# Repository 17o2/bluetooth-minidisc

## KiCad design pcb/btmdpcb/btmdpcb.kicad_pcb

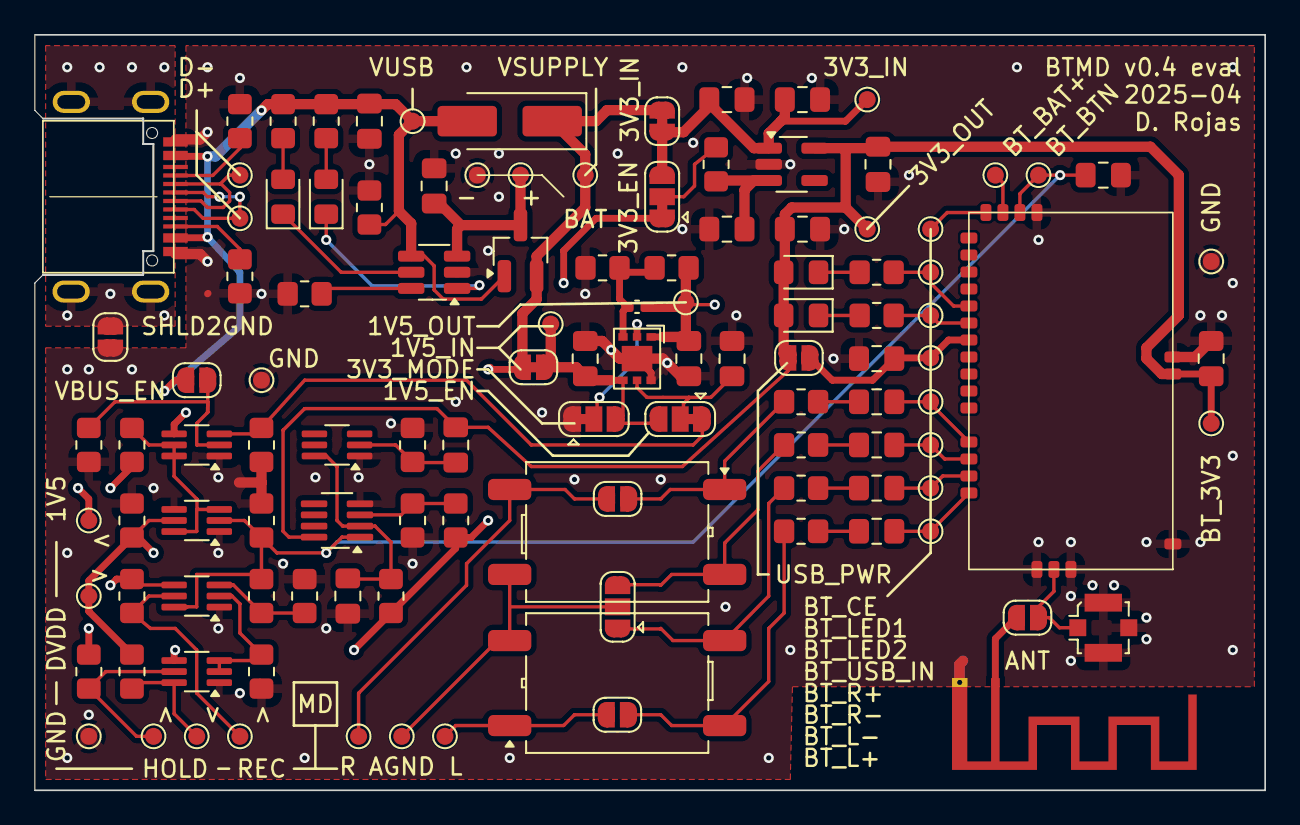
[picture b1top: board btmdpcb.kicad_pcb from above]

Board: 4 copper layers, 72.4 x 44.4 mm, 115 parts (0 on the bottom side), 60 nets.

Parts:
AE1: Antenna_Shield; Texas_SWRA117D_2.4GHz_Left
C1, C6, C11, C12, C14, C15, C16, C17: 1u; C_0805_2012Metric_Pad1.18x1.45mm_HandSolder
C2, C3, C4, C5, C8, C9: 10u; C_0805_2012Metric_Pad1.18x1.45mm_HandSolder
C7: 22p; C_0402_1005Metric_Pad0.74x0.62mm_HandSolder
C10, C13, C18, C19, C20: 100n; C_0805_2012Metric_Pad1.18x1.45mm_HandSolder
D1: GS1A; D_SMA_Handsoldering
J1: USB_C_Receptacle_USB2.0_16P; TYPE-C-31-M-14
JP1: 1V5_IN; SolderJumper-2_P1.3mm_Bridged_RoundedPad1.0x1.5mm
JP2: 3V3_IN; SolderJumper-2_P1.3mm_Bridged_RoundedPad1.0x1.5mm
JP3: 1V5_EN; SolderJumper-3_P1.3mm_Bridged12_RoundedPad1.0x1.5mm
JP4: 3V3_EN; SolderJumper-3_P1.3mm_Bridged12_RoundedPad1.0x1.5mm
JP5: 3V3_MODE; SolderJumper-3_P1.3mm_Bridged12_RoundedPad1.0x1.5mm
JP6: VBUS_EN; SolderJumper-2_P1.3mm_Open_RoundedPad1.0x1.5mm
JP7: SHLD2GND; SolderJumper-2_P1.3mm_Open_RoundedPad1.0x1.5mm
JP8: R_SKIP; SolderJumper-2_P1.3mm_Open_RoundedPad1.0x1.5mm
JP9: AGND_SKIP; SolderJumper-3_P1.3mm_Open_RoundedPad1.0x1.5mm
JP10: L_SKIP; SolderJumper-2_P1.3mm_Open_RoundedPad1.0x1.5mm
JP11: ANT; SolderJumper-2_P1.3mm_Open_RoundedPad1.0x1.5mm
JP12: USB_PWR; SolderJumper-2_P1.3mm_Open_RoundedPad1.0x1.5mm
LED1, LED3, LED4: GN; LED_0805_2012Metric_Pad1.15x1.40mm_HandSolder
LED2: RD; LED_0805_2012Metric_Pad1.15x1.40mm_HandSolder
Q1, Q3: BSD235N; SOT-363_SC-70-6_Handsoldering
Q2, Q4, Q6: BSD235C; SOT-363_SC-70-6_Handsoldering
Q5: AO3401A; SOT-23_Handsoldering
R1, R2, R9: 10k; R_0805_2012Metric_Pad1.20x1.40mm_HandSolder
R3: 330k; R_0805_2012Metric_Pad1.20x1.40mm_HandSolder
R4: 150k; R_0805_2012Metric_Pad1.20x1.40mm_HandSolder
R5: 220k; R_0805_2012Metric_Pad1.20x1.40mm_HandSolder
R7, R8, R10, R11, R12, R13, R14, R20, R21, R31, R32, R33: 100k; R_0805_2012Metric_Pad1.20x1.40mm_HandSolder
R15, R16, R25, R26, R27, R28: 5k1; R_0805_2012Metric_Pad1.20x1.40mm_HandSolder
R17, R18: 330R; R_0805_2012Metric_Pad1.20x1.40mm_HandSolder
R19: 1k6; R_0805_2012Metric_Pad1.20x1.40mm_HandSolder
R22: 115k; R_0805_2012Metric_Pad1.20x1.40mm_HandSolder
R29, R30: 100R; R_0805_2012Metric_Pad1.20x1.40mm_HandSolder
T1, T2: ED8_4; Transformer_ED8_4-Lead_10.5x8mm_P5mm
TP1: D-; TestPoint_Pad_D1.0mm
TP2: D+; TestPoint_Pad_D1.0mm
TP3, TP13, TP28: GND; TestPoint_Pad_D1.0mm
TP4: VUSB; TestPoint_Pad_D1.0mm
TP5: +; TestPoint_Pad_D1.0mm
TP6: -; TestPoint_Pad_D1.0mm
TP7: VSUPPLY; TestPoint_Pad_D1.0mm
TP8: 1V5_IN; TestPoint_Pad_D1.0mm
TP9: 1V5_OUT; TestPoint_Pad_D1.0mm
TP10: 3V3_IN; TestPoint_Pad_D1.0mm
TP11: 3V3_OUT; TestPoint_Pad_D1.0mm
TP12: 1V5; TestPoint_Pad_D1.0mm
TP15, TP21: HOLD; TestPoint_Pad_D1.0mm
TP16: L; TestPoint_Pad_D1.0mm
TP17: R; TestPoint_Pad_D1.0mm
TP18: AGND; TestPoint_Pad_D1.0mm
TP19: DVDD; TestPoint_Pad_D1.0mm
TP20: REC; TestPoint_Pad_D1.0mm
TP22: BT_L+; TestPoint_Pad_D1.0mm
TP23: BT_L-; TestPoint_Pad_D1.0mm
TP24: BT_R-; TestPoint_Pad_D1.0mm
TP25: BT_R+; TestPoint_Pad_D1.0mm
TP26: BT_USB_IN; TestPoint_Pad_D1.0mm
TP27: BT_3V3; TestPoint_Pad_D1.0mm
TP29: BT_BTN; TestPoint_Pad_D1.0mm
TP30: BT_LED1; TestPoint_Pad_D1.0mm
TP31: BT_LED2; TestPoint_Pad_D1.0mm
TP32: BT_BAT+; TestPoint_Pad_D1.0mm
TP33: BT_CE; TestPoint_Pad_D1.0mm
U1: LM393; SOT-23-8_Handsoldering
U2: TP4057; SOT-23-6_Handsoldering
U3: Würth 171010502; U_Wurth_WPME-VDMM_171010502
U4: ME6211C33M5; SOT-23-5_HandSoldering
U5: bt_audio_smd
Y1: ANT; U.FL_Molex_MCRF_73412-0110_Vertical

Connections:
+1V5: C7.1, C8.1, R21.1, TP9.1, TP12.1, U3.1 (VOUT)
+3V3: C1.1, C12.1, C13.1, C19.1, JP12.1 (A), LED3.2 (A), LED4.2 (A), TP11.1, TP27.1, U1.8 (V+), U4.5 (V_{OUT}), U5.11 (3v3_IN)
+SUPPLY: D1.1 (K), JP1.1 (A), JP2.1 (A), Q2.4 (SP), Q4.4 (SP), Q5.2 (S), Q6.4 (SP), R3.1, R4.1, R7.2, R12.1, R31.2, TP7.1
/HOLD: Q2.2 (GN), Q6.2 (GN), Q6.3 (DP), R32.2
/KICKSTART/BT_BTN: C20.2, Q2.6 (DN), Q3.2 (G1), R9.2, R10.1, TP29.1, U1.1, U5.28 (BTN)
/MD unit (MZ-N505)/AUDIO_GND: JP9.2 (C), T1.3, T2.2, TP18.1
/MD unit (MZ-N505)/AUDIO_L: JP10.1 (A), T2.1, TP16.1
/MD unit (MZ-N505)/AUDIO_R: JP8.1 (A), T1.4, TP17.1
/MD unit (MZ-N505)/~SW_HOLD_IN: Q6.6 (DN), R33.1, TP15.1
/REC: Q2.3 (DP), R8.1, R9.1
/bt_module/PWR_EN: TP33.1, U5.30 (CE)
/power_3v3/EN: C11.1, R1.1, U4.3 (CE)
/power_3v3/Vin: C9.1, C10.1, JP2.2 (B), JP4.3 (B), TP10.1, U4.1 (V_{IN})
/power_we/EN: C6.1, JP3.2 (C), U3.5 (EN)
/power_we/MODE: JP5.2 (C), U3.2 (MODE)
/power_we/Vin: C5.1, JP1.2 (B), JP3.3 (B), JP5.3 (B), TP8.1, U3.4 (VIN)
/supply/BAT+: C4.1, Q5.3 (D), TP5.1, U2.3 (BAT)
/supply/CC1: J1.A5 (CC1), R16.1
/supply/CC2: J1.B5 (CC2), R15.1
/supply/D+: J1.A6 (D+), J1.B6 (D+), TP2.1
/supply/D-: J1.A7 (D-), J1.B7 (D-), TP1.1
/supply/SHIELD: J1.S1 (SHIELD), JP7.1 (A)
/~HOLD: Q6.5 (GP), R31.1, TP21.1
/~REC: Q2.5 (GP), R7.1, TP20.1
EN_1V5: JP3.1 (A), Q4.3 (DP), R13.1
GND: AE1.2 (Shield), C2.2, C3.2, C4.2, C5.2, C6.2, C8.2, C9.2, C10.2, C11.2, C12.2, C13.2, C18.2, C19.2, C20.1, J1.A1 (GND), J1.A12 (GND), J1.B1 (GND), J1.B12 (GND), JP5.1 (A), JP7.2 (B), Q1.1 (S1), Q2.1 (SN), Q3.1 (S1), Q3.4 (S2), Q4.1 (SN), Q6.1 (SN), R2.2, R5.2, R8.2, R10.2, R11.2, R13.2, R14.2, R15.2, R16.2, R19.2, R20.2, R22.2, R32.1, TP3.1, TP6.1, TP13.1, TP28.1, U1.4 (V-), U2.2 (GND), U3.6 (PGND), U3.EP (PGND), U4.2 (V_{SS}), U5.1 (GND), U5.12 (GND), U5.27 (GND), U5.50 (GND), U5.52 (GND), Y1.2 (Ext)
unnamed: AE1.1 (A), JP11.1 (A)
unnamed: C14.1, R25.2
unnamed: C15.1, R26.2
unnamed: C16.1, R27.2
unnamed: C17.1, R28.2
unnamed: JP4.2 (C), R1.2
unnamed: JP6.1 (A), Q4.2 (GN), R14.1
unnamed: JP8.2 (B), R28.1, T1.1
unnamed: JP9.1 (A), R26.1, T2.3
unnamed: JP9.3 (B), R27.1, T1.2
unnamed: JP10.2 (B), R25.1, T2.4
unnamed: JP11.2 (B), U5.51 (ANT), Y1.1 (In)
unnamed: C18.1, JP12.2 (B), TP26.1, U5.37 (USB_IN)
unnamed: LED1.2 (A), R17.2
unnamed: LED1.1 (K), U2.5 (STDBY)
unnamed: LED2.2 (A), R18.2
unnamed: LED2.1 (K), U2.1 (~CHRG)
unnamed: LED3.1 (K), R29.2
unnamed: LED4.1 (K), R30.1
unnamed: C2.1, Q1.6 (D1), R3.2, U1.2 (-)
unnamed: C1.2, Q1.2 (G1), R2.1
unnamed: R4.2, R5.1, U1.3 (+)
unnamed: R19.1, U2.6 (PROG)
unnamed: C7.2, R21.2, R22.1, U3.3 (FB)
unnamed: TP32.1, U5.29 (BAT+)
unnamed: C14.2, TP22.1, U5.46 (L+)
unnamed: C15.2, TP23.1, U5.45 (L-)
unnamed: R29.1, TP30.1, U5.35 (LED1)
unnamed: R30.2, TP31.1, U5.36 (LED2)
unnamed: C17.2, TP25.1, U5.43 (R+)
unnamed: C16.2, TP24.1, U5.44 (R-)
VBUS: C3.1, D1.2 (A), J1.A4 (VBUS), J1.A9 (VBUS), J1.B4 (VBUS), J1.B9 (VBUS), JP6.2 (B), Q5.1 (G), R17.1, R18.1, R20.1, TP4.1, U2.4 (V_{CC})
VDD: JP4.1 (A), Q3.5 (G2), R11.1, R33.2, TP19.1
~EN_1V5: Q3.3 (D2), Q3.6 (D1), Q4.5 (GP), Q4.6 (DN), R12.2

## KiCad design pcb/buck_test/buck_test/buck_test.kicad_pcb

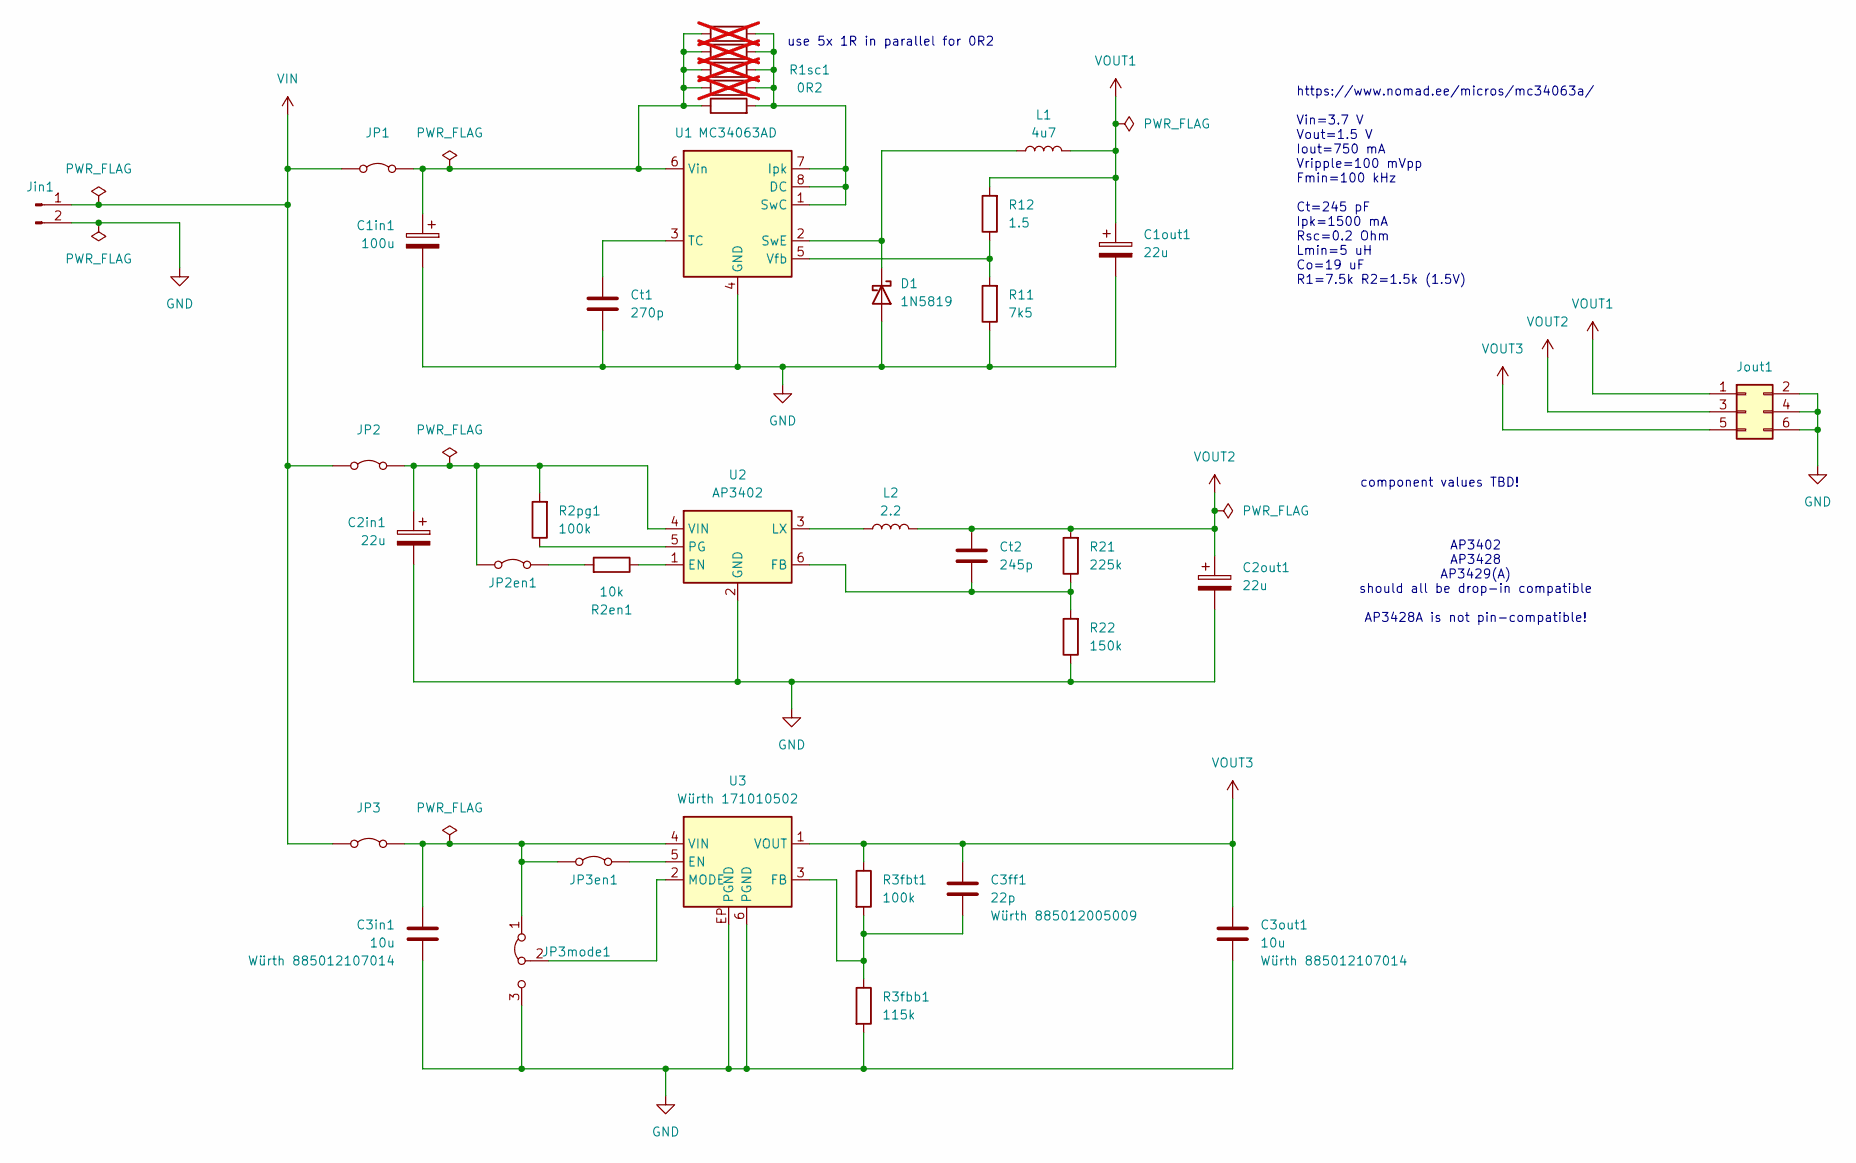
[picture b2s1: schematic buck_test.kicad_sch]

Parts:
C1in1: 100u; C_Elec_6.3x7.7
C1out1, C2in1, C2out1: 22u; C_Elec_6.3x5.4
C3ff1: 22p; C_0603_1608Metric_Pad1.08x0.95mm_HandSolder
C3in1, C3out1: 10u; C_0805_2012Metric_Pad1.18x1.45mm_HandSolder
Ct1: 270p; C_0805_2012Metric_Pad1.18x1.45mm_HandSolder
Ct2: 245p; C_0805_2012Metric_Pad1.18x1.45mm_HandSolder
D1: 1N5819; D_SMA
JP1, JP2, JP2en1, JP3, JP3en1: Jumper_2_Bridged; PinHeader_1x02_P2.54mm_Vertical
JP3mode1: Jumper_3_Bridged12; PinHeader_1x03_P2.54mm_Vertical
Jin1: Conn_01x02_Pin; PinHeader_1x02_P2.54mm_Vertical
Jout1: Conn_02x03_Odd_Even; PinHeader_2x03_P2.54mm_Vertical
L1: 4u7
L2: 2.2
R1sc1: 0R2; R_0805_2012Metric_Pad1.20x1.40mm_HandSolder
R1sc2, R1sc3, R1sc4, R1sc5: 0R2; R_0805_2012Metric_Pad1.20x1.40mm_HandSolder; not fitted
R2en1: 10k; R_0805_2012Metric_Pad1.20x1.40mm_HandSolder
R2pg1, R3fbt1: 100k; R_0805_2012Metric_Pad1.20x1.40mm_HandSolder
R3fbb1: 115k; R_0805_2012Metric_Pad1.20x1.40mm_HandSolder
R11: 7k5; R_0805_2012Metric_Pad1.20x1.40mm_HandSolder
R12: 1.5; R_0805_2012Metric_Pad1.20x1.40mm_HandSolder
R21: 225k; R_0805_2012Metric_Pad1.20x1.40mm_HandSolder
R22: 150k; R_0805_2012Metric_Pad1.20x1.40mm_HandSolder
U1: MC34063AD; SOIC-8_3.9x4.9mm_P1.27mm
U2: AP3402; TSOT-23-6
U3: Würth 171010502; U_Wurth_WPME-VDMM_171010502

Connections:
GND: C1in1.2, C1out1.2, C2in1.2, C2out1.2, C3in1.2, C3out1.2, Ct1.2, D1.2 (A), JP3mode1.3 (B), Jin1.2, Jout1.2, Jout1.4, Jout1.6, R3fbb1.2, R11.1, R22.1, U1.4 (GND), U2.2 (GND), U3.6 (PGND), U3.EP (PGND)
unnamed: D1.1 (K), L1.1, U1.2 (SwE)
unnamed: C1in1.1, JP1.2 (B), R1sc1.1, R1sc2.1, R1sc3.1, R1sc4.1, R1sc5.1, U1.6 (Vin)
unnamed: C2in1.1, JP2.2 (B), JP2en1.1 (A), R2pg1.2, U2.4 (VIN)
unnamed: JP2en1.2 (B), R2en1.2
unnamed: C3in1.1, JP3.2 (B), JP3en1.1 (A), JP3mode1.1 (A), U3.4 (VIN)
unnamed: JP3en1.2 (B), U3.5 (EN)
unnamed: JP3mode1.2 (C), U3.2 (MODE)
unnamed: R1sc1.2, R1sc2.2, R1sc3.2, R1sc4.2, R1sc5.2, U1.1 (SwC), U1.7 (Ipk), U1.8 (DC)
unnamed: Ct1.1, U1.3 (TC)
unnamed: R11.2, R12.1, U1.5 (Vfb)
unnamed: R2en1.1, U2.1 (EN)
unnamed: Ct2.2, R21.1, R22.2, U2.6 (FB)
unnamed: L2.1, U2.3 (LX)
unnamed: R2pg1.1, U2.5 (PG)
unnamed: C3ff1.2, R3fbb1.1, R3fbt1.2, U3.3 (FB)
VIN: JP1.1 (A), JP2.1 (A), JP3.1 (A), Jin1.1
VOUT1: C1out1.1, Jout1.1, L1.2, R12.2
VOUT2: C2out1.1, Ct2.1, Jout1.3, L2.2, R21.2
VOUT3: C3ff1.1, C3out1.1, Jout1.5, R3fbt1.1, U3.1 (VOUT)

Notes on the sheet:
AP3402 AP3428 AP3429(A) should all be drop-in compatible AP3428A is not pin-compatible!
component values TBD!
https://www.nomad.ee/micros/mc34063a/ Vin=3.7 V Vout=1.5 V Iout=750 mA Vripple=100 mVpp Fmin=100 kHz Ct=245 pF Ipk=1500 mA Rsc=0.2 Ohm Lmin=5 uH Co=19 uF R1=7.5k R2=1.5k (1.5V)
use 5x 1R in parallel for 0R2

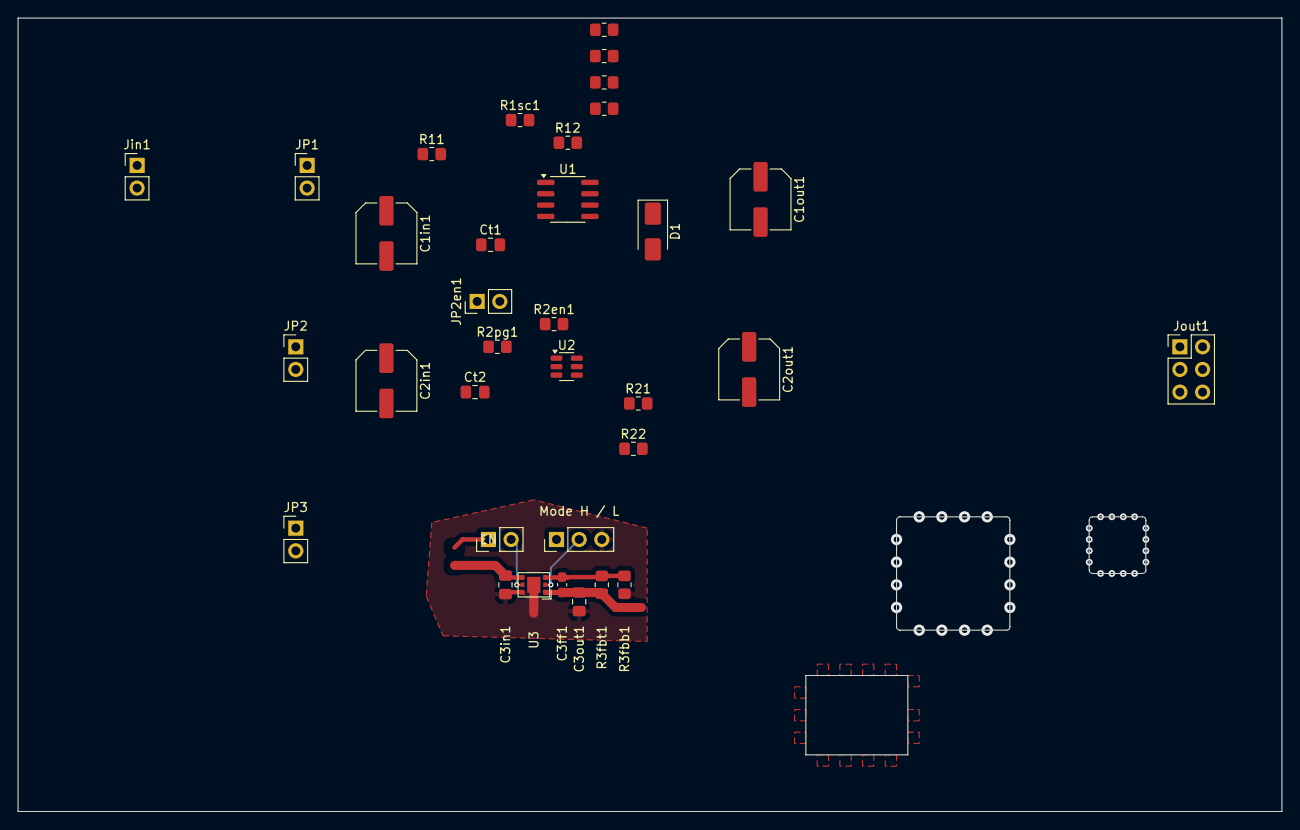
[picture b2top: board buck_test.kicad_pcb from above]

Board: 2 copper layers, 141.6 x 88.9 mm, 34 parts (0 on the bottom side), 19 nets.

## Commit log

2025-04-01 [WIP] Redo schematic for powering from 3.7V LiPo
2025-04-01 [WIP] Design eval board for step-down converters, other features
2025-04-01 [WIP] Tests to allow mounting BT module coplanar with PCB
2025-04-01 Remove redundant regulators, simplify schematic
2025-04-01 Separate BT and Pololu libraries
2025-04-01 First draft of v0.4 PCB
2025-04-01 Update BT module symbol+footprint (correct power labels, add CE)
2025-04-01 Clean up schematic, implement all logic functionality
2025-04-01 [WIP] Design eval board for all relevant functions
2025-04-04 Use REC instead of PAUSE for power kickstart
2025-04-04 Simplify circuit; reduce transistor count
2025-04-04 Add BT auto-powerup (RC circuit + comparator)
2025-04-04 Create and use BSD235N symbol
    to replace 2N7000 N-MOSFETS used temporarily up to now
2025-04-04 Add missing libraries, assign all footprints
2025-04-04 Correct footprints, fix issues on update PCB from schematic
2025-04-05 Add JLCPCB design rules
2025-04-06 Layout PCB
2025-04-06 Fix connectors & clearance; touch up PCB
2025-04-06 Export gerbers, order PCB
2025-04-06 Rename v0.4 eval board KiCad project
2025-04-06 Remove buck converter test project
2025-04-06 Move v0.3 firmware into dedicated subfolder
2025-04-06 Add Aisler ID (test only)
    testing Push to Aisler plugin
